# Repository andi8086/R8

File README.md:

## Picocom configuration ##

Start picocom with:

```
picocom --send-cmd "sx -Xb" -b 19200 -d 8 --emap lfcr /dev/ttyUSB0
```

## XMODEM File transfer ##

```
REICHEL R8
6502 CPU @ 2 MHz
32K RAM         
MONITOR (c)1976 Steve Wozniak
ADAPTED 2017 Andreas J. Reichel
\                              
F900R
F900: 20XMOD
CCCC
*** file: /home/andreas/Projects/6502/testprogs/test1.bin
$ sx -Xb /home/andreas/Projects/6502/testprogs/test1.bin 
Sending /home/andreas/Projects/6502/testprogs/test1.bin, 0 blocks: Give your local XMODEM receive command now.
Xmodem sectors/kbytes sent:   0/ 0kRetry 0: NAK on sector
Bytes Sent:    128   BPS:75                              

Transfer complete

*** exit status: 0 ***
OK
\
1000.1020
1000: A9 0E 85 20 A9 10 85 21
1008: 20 2F C0 4C 00 F8 48 69
1010: 2C 20 49 20 61 6D 20 74
1018: 68 65 20 66 69 72 73 74
1020: 20                     
1000    
1000: A9
Hi, I am the first program transfered via serial :)
\                                                  
```

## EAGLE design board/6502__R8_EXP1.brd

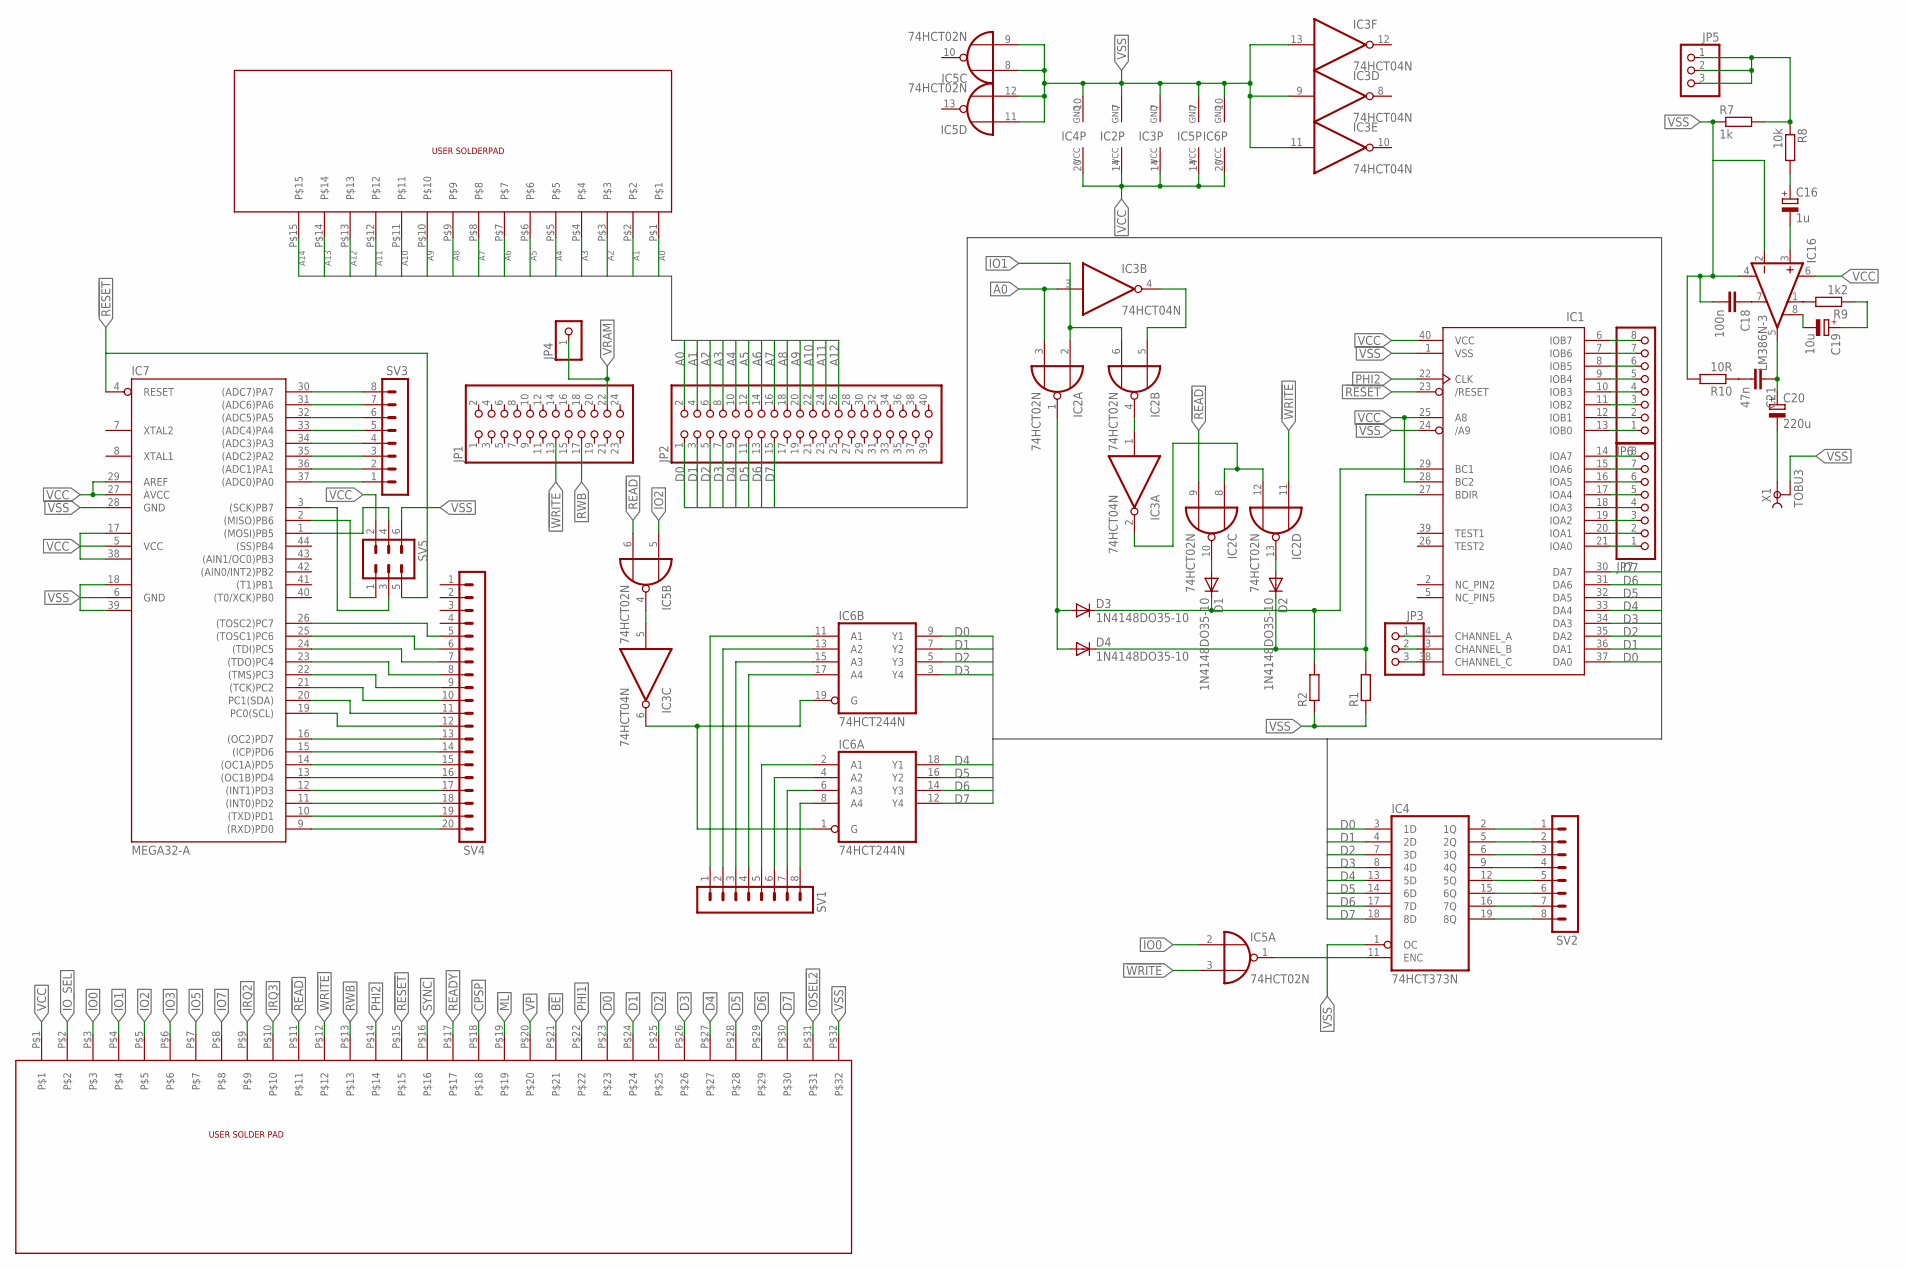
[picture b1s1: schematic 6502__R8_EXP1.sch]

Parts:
C16: 1u; E5-5
C18: 100n; C025-030X050
C19: 10u; E5-5
C20: 220u; E5-5
C21: 47n; C025-030X050
D1, D2, D3, D4: 1N4148DO35-10; DO35-10
IC1: AY-3-8910; DIL40
IC2, IC5: 74HCT02N; DIL14
IC3: 74HCT04N; DIL14
IC4: 74HCT373N; DIL20
IC6: 74HCT244N; DIL20
IC7: MEGA32-A; TQFP44
IC16: LM386N-3; DIL08
JP1: PINHD-2X12; 2X12
JP2: PINHD-2X20; 2X20
JP3, JP5: PINHD-1X3; 1X03
JP4: PINHD-1X1; 1X01
JP6, JP7: PINHD-1X8; 1X08
R1, R2: R-EU_0204/7; 0204/7
R7: 1k; 0207/12
R8: 10k; 0207/12
R9: 1k2; 0207/12
R10: 10R; 0207/12
SV1, SV2, SV3: MA08-1
SV4: MA20-1
SV5: MA03-2
U$2: SOLDERPAD
U$3: SOLDERPAD2
X1: TOBU3

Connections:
!BE: U$2.P$21
!IOSEL2: U$2.P$31
!ML: U$2.P$19
!READ: IC2.9 (I1), IC5.6 (I1), U$2.P$11
!RESET: IC1.23 (/RESET), IC7.4 (RESET), SV5.5, U$2.P$15
!VP: U$2.P$20
!VRAM: JP1.22, JP4.1
!WRITE: IC2.11 (I0), IC5.3 (I1), JP1.13, U$2.P$12
A0: IC2.3 (I1), IC3.3 (I), JP2.2, U$3.P$1
A1: JP2.4, U$3.P$2
A2: JP2.6, U$3.P$3
A3: JP2.8, U$3.P$4
A4: JP2.10, U$3.P$5
A5: JP2.12, U$3.P$6
A6: JP2.14, U$3.P$7
A7: JP2.16, U$3.P$8
A8: JP2.18, U$3.P$9
A9: JP2.20, U$3.P$10
A10: JP2.22, U$3.P$11
A11: JP2.24, U$3.P$12
A12: JP2.26, U$3.P$13
A13: U$3.P$14
A14: U$3.P$15
CPSP: U$2.P$18
D0: IC1.37 (DA0), IC4.3 (1D), IC6.9 (Y1), JP2.1, U$2.P$23
D1: IC1.36 (DA1), IC4.4 (2D), IC6.7 (Y2), JP2.3, U$2.P$24
D2: IC1.35 (DA2), IC4.7 (3D), IC6.5 (Y3), JP2.5, U$2.P$25
D3: IC1.34 (DA3), IC4.8 (4D), IC6.3 (Y4), JP2.7, U$2.P$26
D4: IC1.33 (DA4), IC4.13 (5D), IC6.18 (Y1), JP2.9, U$2.P$27
D5: IC1.32 (DA5), IC4.14 (6D), IC6.16 (Y2), JP2.11, U$2.P$28
D6: IC1.31 (DA6), IC4.17 (7D), IC6.14 (Y3), JP2.13, U$2.P$29
D7: IC1.30 (DA7), IC4.18 (8D), IC6.12 (Y4), JP2.15, U$2.P$30
IO0: IC5.2 (I0), U$2.P$3
IO1: IC2.2 (I0), IC2.6 (I1), U$2.P$4
IO2: IC5.5 (I0), U$2.P$5
IO3: U$2.P$6
IO5: U$2.P$7
IO7: U$2.P$8
IO_SEL: U$2.P$2
IRQ2: U$2.P$9
IRQ3: U$2.P$10
unnamed: IC4.11 (ENC), IC5.1 (O)
unnamed: IC6.11 (A1), SV1.1
unnamed: IC2.5 (I0), IC3.4 (O)
unnamed: IC2.4 (O), IC3.1 (I)
unnamed: IC2.8 (I0), IC2.12 (I1), IC3.2 (O)
unnamed: IC6.13 (A2), SV1.2
unnamed: D3.A, D4.A, IC2.1 (O)
unnamed: D1.C, D3.C, IC1.29 (BC1), R2.2
unnamed: D2.C, D4.C, IC1.27 (BDIR), R1.2
unnamed: D1.A, IC2.10 (O)
unnamed: D2.A, IC2.13 (O)
unnamed: IC6.15 (A3), SV1.3
unnamed: IC6.17 (A4), SV1.4
unnamed: IC6.2 (A1), SV1.5
unnamed: IC6.4 (A2), SV1.6
unnamed: IC6.6 (A3), SV1.7
unnamed: IC6.8 (A4), SV1.8
unnamed: IC3.5 (I), IC5.4 (O)
unnamed: IC3.6 (O), IC6.1 (G), IC6.19 (G)
unnamed: IC4.2 (1Q), SV2.1
unnamed: IC4.5 (2Q), SV2.2
unnamed: IC4.6 (3Q), SV2.3
unnamed: IC4.9 (4Q), SV2.4
unnamed: IC4.12 (5Q), SV2.5
unnamed: IC4.15 (6Q), SV2.6
unnamed: IC4.16 (7Q), SV2.7
unnamed: IC4.19 (8Q), SV2.8
unnamed: IC1.4 (CHANNEL_A), JP3.1
unnamed: IC1.3 (CHANNEL_B), JP3.2
unnamed: IC1.38 (CHANNEL_C), JP3.3
unnamed: IC1.13 (IOB0), JP6.1
unnamed: IC7.37 ((ADC0)PA0), SV3.1
unnamed: IC7.36 ((ADC1)PA1), SV3.2
unnamed: IC7.35 ((ADC2)PA2), SV3.3
unnamed: IC7.9 ((RXD)PD0), SV4.20
unnamed: IC7.10 ((TXD)PD1), SV4.19
unnamed: IC7.11 ((INT0)PD2), SV4.18
unnamed: IC7.12 ((INT1)PD3), SV4.17
unnamed: IC7.13 ((OC1B)PD4), SV4.16
unnamed: IC7.14 ((OC1A)PD5), SV4.15
unnamed: IC7.15 ((ICP)PD6), SV4.14
unnamed: IC7.16 ((OC2)PD7), SV4.13
unnamed: IC7.19 (PC0(SCL)), SV4.12
unnamed: IC7.20 (PC1(SDA)), SV4.11
unnamed: IC7.21 ((TCK)PC2), SV4.10
unnamed: IC7.22 ((TMS)PC3), SV4.9
unnamed: IC7.23 ((TDO)PC4), SV4.8
unnamed: IC7.24 ((TDI)PC5), SV4.7
unnamed: IC7.25 ((TOSC1)PC6), SV4.6
unnamed: IC7.26 ((TOSC2)PC7), SV4.5
unnamed: IC7.2 ((MISO)PB6), SV5.1
unnamed: IC7.3 ((SCK)PB7), SV5.3
unnamed: IC7.34 ((ADC3)PA3), SV3.4
unnamed: IC7.1 ((MOSI)PB5), SV5.4
unnamed: IC7.33 ((ADC4)PA4), SV3.5
unnamed: IC7.32 ((ADC5)PA5), SV3.6
unnamed: IC7.31 ((ADC6)PA6), SV3.7
unnamed: IC7.30 ((ADC7)PA7), SV3.8
unnamed: IC1.12 (IOB1), JP6.2
unnamed: IC1.11 (IOB2), JP6.3
unnamed: IC1.10 (IOB3), JP6.4
unnamed: IC1.9 (IOB4), JP6.5
unnamed: IC1.8 (IOB5), JP6.6
unnamed: IC1.7 (IOB6), JP6.7
unnamed: IC1.6 (IOB7), JP6.8
unnamed: IC1.21 (IOA0), JP7.1
unnamed: IC1.20 (IOA1), JP7.2
unnamed: IC1.19 (IOA2), JP7.3
unnamed: IC1.18 (IOA3), JP7.4
unnamed: IC1.17 (IOA4), JP7.5
unnamed: IC1.16 (IOA5), JP7.6
unnamed: IC1.15 (IOA6), JP7.7
unnamed: IC1.14 (IOA7), JP7.8
unnamed: JP5.1, JP5.2, JP5.3, R7.2, R8.1
unnamed: C16.+, R8.2
unnamed: C16.-, IC16.3 (+IN)
unnamed: C18.1, IC16.7 (BYPASS)
unnamed: C19.-, IC16.8 (GAIN)
unnamed: IC16.1 (GAIN), R9.2
unnamed: C19.+, R9.1
unnamed: C20.-, X1.1
unnamed: C20.+, C21.1, IC16.5 (OUT)
unnamed: C21.2, R10.1
PHI1: U$2.P$22
PHI2: IC1.22 (CLK), U$2.P$14
READY: U$2.P$17
RWB: JP1.17, U$2.P$13
SYNC: U$2.P$16
VCC: IC1.25 (A8), IC1.28 (BC2), IC1.40 (VCC), IC2.14 (VCC), IC3.14 (VCC), IC4.20 (VCC), IC5.14 (VCC), IC6.20 (VCC), IC7.5 (VCC), IC7.17 (VCC1), IC7.27 (AVCC), IC7.29 (AREF), IC7.38 (VCC2), IC16.6 (VS), SV5.2, U$2.P$1

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
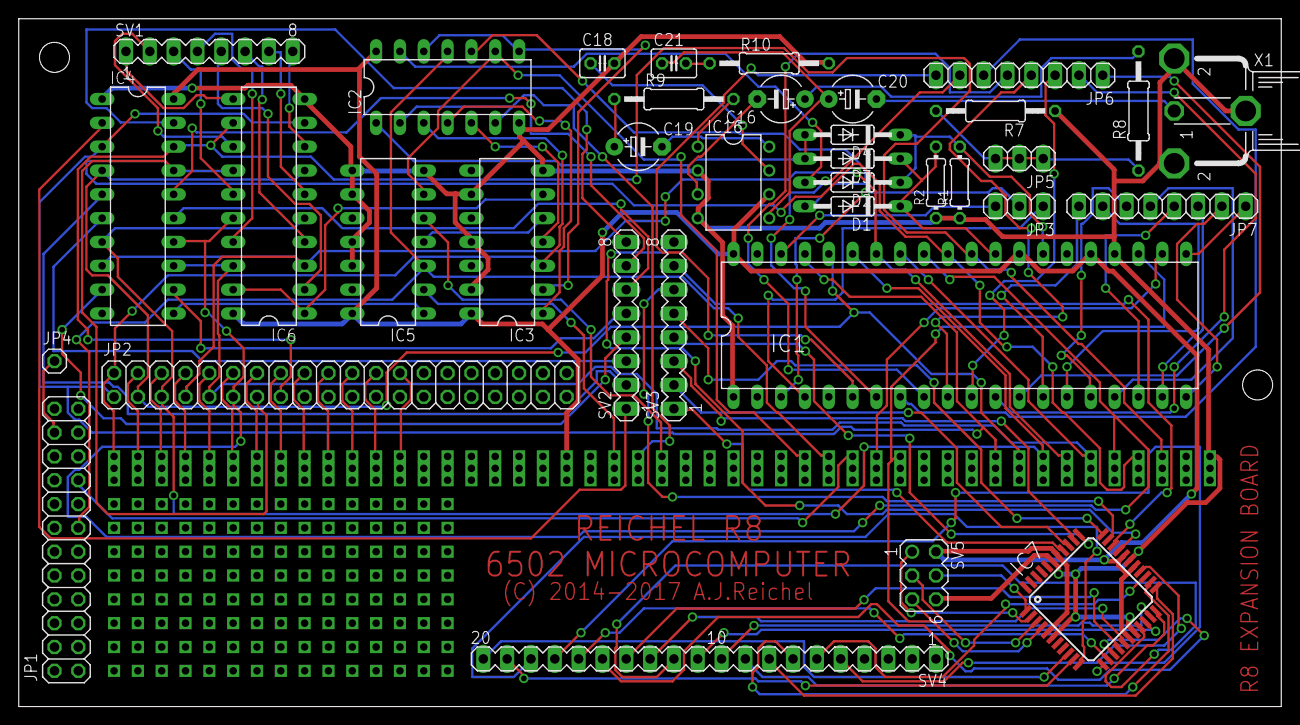
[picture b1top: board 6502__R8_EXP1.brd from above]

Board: 2 copper layers, 134.6 x 73.3 mm, 38 parts (0 on the bottom side), 115 nets.

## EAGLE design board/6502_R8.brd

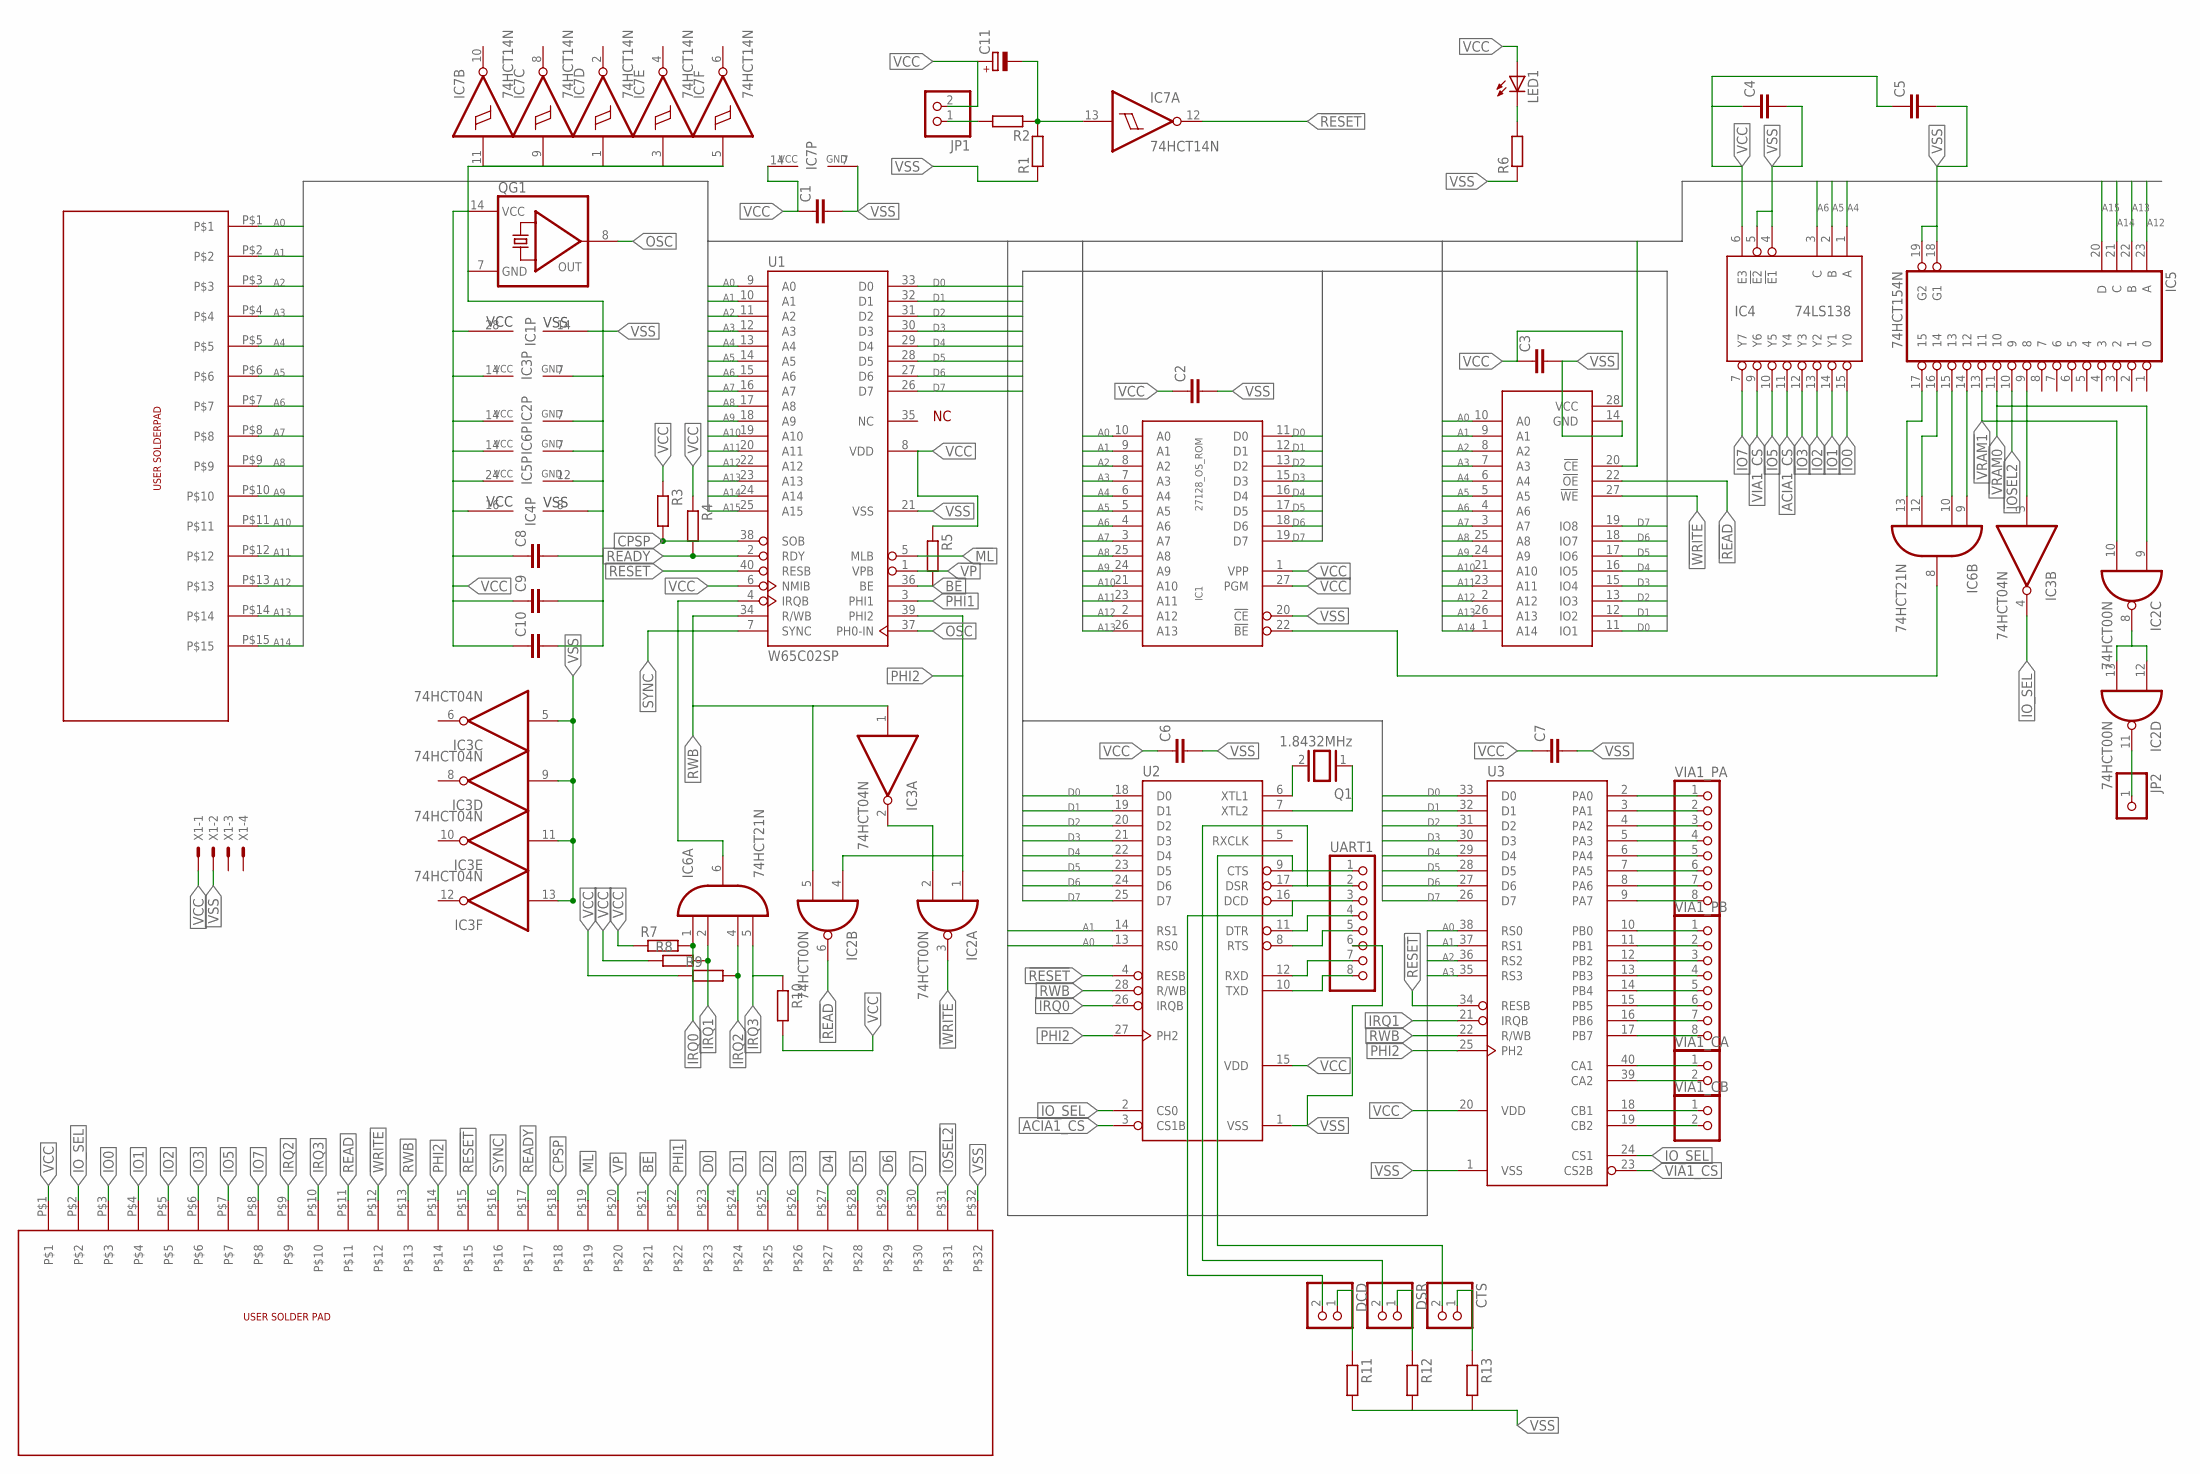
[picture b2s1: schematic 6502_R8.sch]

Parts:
C1, C2, C3, C4, C5, C6, C7, C8, C9, C10: C-EU025-024X044; C025-024X044
C11: CPOL-EUTT2D7; TT2D7
CTS: PINHD-1X2; 1X02
DCD: PINHD-1X2; 1X02
DSR: PINHD-1X2; 1X02
IC1: 27128_OS_ROM; DIL28
IC2: 74HCT00N; DIL14
IC3: 74HCT04N; DIL14
IC4: 74LS138; DIL16
IC5: 74HCT154N; DIL24-6
IC6: 74HCT21N; DIL14
IC7: 74HCT14N; DIL14
JP1: PINHD-1X2; 1X02
JP2: PINHD-1X1; 1X01
LED1: LED5MM
Q1: 1.8432MHz; Q
QG1: QG5860; DIL14S
R1, R2, R3, R4, R5, R6, R7, R8, R9, R10, R11, R12, R13: R-EU_0207/7; 0207/7
U1: W65C02SP; DIP-40
U2: G65SC51P; DIP-28
U3: G65SC22P; DIP-40
U$1: CXK58258AP-20; DIL28-3
U$2: SOLDERPAD
U$3: SOLDERPAD2
UART1: PINHD-1X8; 1X08
VIA1_CA, VIA1_CB: PINHD-1X2; 1X02
VIA1_PA, VIA1_PB: PINHD-1X8; 1X08
X1: KK-156-4

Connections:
!BE: U$2.P$21
!IOSEL2: IC5.10 (9), U$2.P$31
!ML: U1.5 (MLB), U$2.P$19
!READ: IC2.6 (O), U$1.22 (!OE), U$2.P$11
!RESET: IC7.12 (O), U1.40 (RESB), U2.4 (RESB), U3.34 (RESB), U$2.P$15
!VP: U1.1 (VPB), U$2.P$20
!VRAM0: IC2.9 (I0), IC5.11 (10)
!VRAM1: IC2.10 (I1), IC5.13 (11)
!WRITE: IC2.3 (O), U$1.27 (!WE), U$2.P$12
A0: IC1.10 (A0), U1.9 (A0), U2.13 (RS0), U3.38 (RS0), U$1.10 (A0), U$3.P$1
A1: IC1.9 (A1), U1.10 (A1), U2.14 (RS1), U3.37 (RS1), U$1.9 (A1), U$3.P$2
A2: IC1.8 (A2), U1.11 (A2), U3.36 (RS2), U$1.8 (A2), U$3.P$3
A3: IC1.7 (A3), U1.12 (A3), U3.35 (RS3), U$1.7 (A3), U$3.P$4
A4: IC1.6 (A4), IC4.1 (A), U1.13 (A4), U$1.6 (A4), U$3.P$5
A5: IC1.5 (A5), IC4.2 (B), U1.14 (A5), U$1.5 (A5), U$3.P$6
A6: IC1.4 (A6), IC4.3 (C), U1.15 (A6), U$1.4 (A6), U$3.P$7
A7: IC1.3 (A7), U1.16 (A7), U$1.3 (A7), U$3.P$8
A8: IC1.25 (A8), U1.17 (A8), U$1.25 (A8), U$3.P$9
A9: IC1.24 (A9), U1.18 (A9), U$1.24 (A9), U$3.P$10
A10: IC1.21 (A10), U1.19 (A10), U$1.21 (A10), U$3.P$11
A11: IC1.23 (A11), U1.20 (A11), U$1.23 (A11), U$3.P$12
A12: IC1.2 (A12), IC5.23 (A), U1.22 (A12), U$1.2 (A12), U$3.P$13
A13: IC1.26 (A13), IC5.22 (B), U1.23 (A13), U$1.26 (A13), U$3.P$14
A14: IC5.21 (C), U1.24 (A14), U$1.1 (A14), U$3.P$15
A15: IC5.20 (D), U1.25 (A15), U$1.20 (!CE)
ACIA1_CS: IC4.11 (Y4), U2.3 (CS1B)
BE: R5.2, U1.36 (BE)
CPSP: R3.2, U1.38 (SOB), U$2.P$18
D0: IC1.11 (D0), U1.33 (D0), U2.18 (D0), U3.33 (D0), U$1.11 (IO1), U$2.P$23
D1: IC1.12 (D1), U1.32 (D1), U2.19 (D1), U3.32 (D1), U$1.12 (IO2), U$2.P$24
D2: IC1.13 (D2), U1.31 (D2), U2.20 (D2), U3.31 (D2), U$1.13 (IO3), U$2.P$25
D3: IC1.15 (D3), U1.30 (D3), U2.21 (D3), U3.30 (D3), U$1.15 (IO4), U$2.P$26
D4: IC1.16 (D4), U1.29 (D4), U2.22 (D4), U3.29 (D4), U$1.16 (IO5), U$2.P$27
D5: IC1.17 (D5), U1.28 (D5), U2.23 (D5), U3.28 (D5), U$1.17 (IO6), U$2.P$28
D6: IC1.18 (D6), U1.27 (D6), U2.24 (D6), U3.27 (D6), U$1.18 (IO7), U$2.P$29
D7: IC1.19 (D7), U1.26 (D7), U2.25 (D7), U3.26 (D7), U$1.19 (IO8), U$2.P$30
IO0: IC4.15 (Y0), U$2.P$3
IO1: IC4.14 (Y1), U$2.P$4
IO2: IC4.13 (Y2), U$2.P$5
IO3: IC4.12 (Y3), U$2.P$6
IO5: IC4.10 (Y5), U$2.P$7
IO7: IC4.7 (Y7), U$2.P$8
IO_SEL: IC3.4 (O), U2.2 (CS0), U3.24 (CS1), U$2.P$2
IRQ0: IC6.1 (I0), R7.2, U2.26 (IRQB)
IRQ1: IC6.2 (I1), R8.2, U3.21 (IRQB)
IRQ2: IC6.4 (I2), R9.2, U$2.P$9
IRQ3: IC6.5 (I3), R10.1, U$2.P$10
unnamed: IC3.3 (I), IC5.9 (8)
unnamed: IC5.17 (15), IC6.13 (I3)
unnamed: IC5.16 (14), IC6.12 (I2)
unnamed: IC5.15 (13), IC6.10 (I1)
unnamed: IC5.14 (12), IC6.9 (I0)
unnamed: IC1.22 (!BE), IC6.8 (O)
unnamed: IC2.2 (I1), IC3.2 (O)
unnamed: Q1.2, U2.6 (XTL1)
unnamed: Q1.1, U2.7 (XTL2)
unnamed: IC6.6 (O), U1.4 (IRQB)
unnamed: IC2.8 (O), IC2.12 (I0), IC2.13 (I1)
unnamed: IC2.11 (O), JP2.1
unnamed: U3.2 (PA0), VIA1_PA.1
unnamed: C11.-, IC7.13 (I), R1.2, R2.1
unnamed: JP1.1, R2.2
unnamed: U3.3 (PA1), VIA1_PA.2
unnamed: U3.4 (PA2), VIA1_PA.3
unnamed: LED1.K (C), R6.2
unnamed: U3.5 (PA3), VIA1_PA.4
unnamed: U3.6 (PA4), VIA1_PA.5
unnamed: U3.7 (PA5), VIA1_PA.6
unnamed: U3.8 (PA6), VIA1_PA.7
unnamed: U3.9 (PA7), VIA1_PA.8
unnamed: U3.10 (PB0), VIA1_PB.1
unnamed: U3.11 (PB1), VIA1_PB.2
unnamed: U3.12 (PB2), VIA1_PB.3
unnamed: U3.13 (PB3), VIA1_PB.4
unnamed: U3.14 (PB4), VIA1_PB.5
unnamed: U3.15 (PB5), VIA1_PB.6
unnamed: U3.16 (PB6), VIA1_PB.7
unnamed: U3.17 (PB7), VIA1_PB.8
unnamed: U3.40 (CA1), VIA1_CA.1
unnamed: U3.39 (CA2), VIA1_CA.2
unnamed: U3.18 (CB1), VIA1_CB.1
unnamed: U3.19 (CB2), VIA1_CB.2
unnamed: U2.10 (TXD), UART1.8
unnamed: U2.12 (RXD), UART1.7
unnamed: CTS.2, U2.9 (CTS), UART1.1
unnamed: DSR.2, U2.17 (DSR), UART1.2
unnamed: DCD.2, U2.16 (DCD), UART1.3
unnamed: U2.11 (DTR), UART1.4
unnamed: U2.8 (RTS), UART1.5
unnamed: DCD.1, R11.1
unnamed: DSR.1, R12.1
unnamed: CTS.1, R13.1
OSC: QG1.8 (OUT), U1.37 (PH0-IN)
PHI1: U1.3 (PHI1), U$2.P$22
PHI2: IC2.1 (I0), IC2.4 (I0), U1.39 (PHI2), U2.27 (PH2), U3.25 (PH2), U$2.P$14
READY: R4.2, U1.2 (RDY), U$2.P$17
RWB: IC2.5 (I1), IC3.1 (I), U1.34 (R/WB), U2.28 (R/WB), U3.22 (R/WB), U$2.P$13
SYNC: U1.7 (SYNC), U$2.P$16
VCC: C1.1, C2.1, C3.1, C4.1, C5.1, C6.1, C7.1, C8.1, C9.1, C10.1, C11.+, IC1.1 (VPP), IC1.27 (PGM), IC1.28 (VCC), IC2.14 (VCC), IC3.14 (VCC), IC4.6 (E3), IC4.16 (VCC), IC5.24 (VCC), IC6.14 (VCC), IC7.14 (VCC), JP1.2, LED1.A, QG1.14 (VCC), R3.1, R4.1, R5.1, R7.1, R8.1, R9.1, R10.2, U1.6 (NMIB), U1.8 (VDD), U2.15 (VDD), U3.20 (VDD), U$1.28 (VCC), U$2.P$1, X1.1
VIA1_CS: IC4.9 (Y6), U3.23 (CS2B)
VSS: C1.2, C2.2, C3.2, C4.2, C5.2, C6.2, C7.2, C8.2, C9.2, C10.2, IC1.14 (VSS), IC1.20 (!CE), IC2.7 (GND), IC3.5 (I), IC3.7 (GND), IC3.9 (I), IC3.11 (I), IC3.13 (I), IC4.4 (!E1), IC4.5 (!E2), IC4.8 (VSS), IC5.12 (GND), IC5.18 (G1), IC5.19 (G2), IC6.7 (GND), IC7.1 (I), IC7.3 (I), IC7.5 (I), IC7.7 (GND), IC7.9 (I), IC7.11 (I), QG1.7 (GND), R1.1, R6.1, R11.2, R12.2, R13.2, U1.21 (VSS), U2.1 (VSS), U3.1 (VSS), U$1.14 (GND), U$2.P$32, UART1.6, X1.2

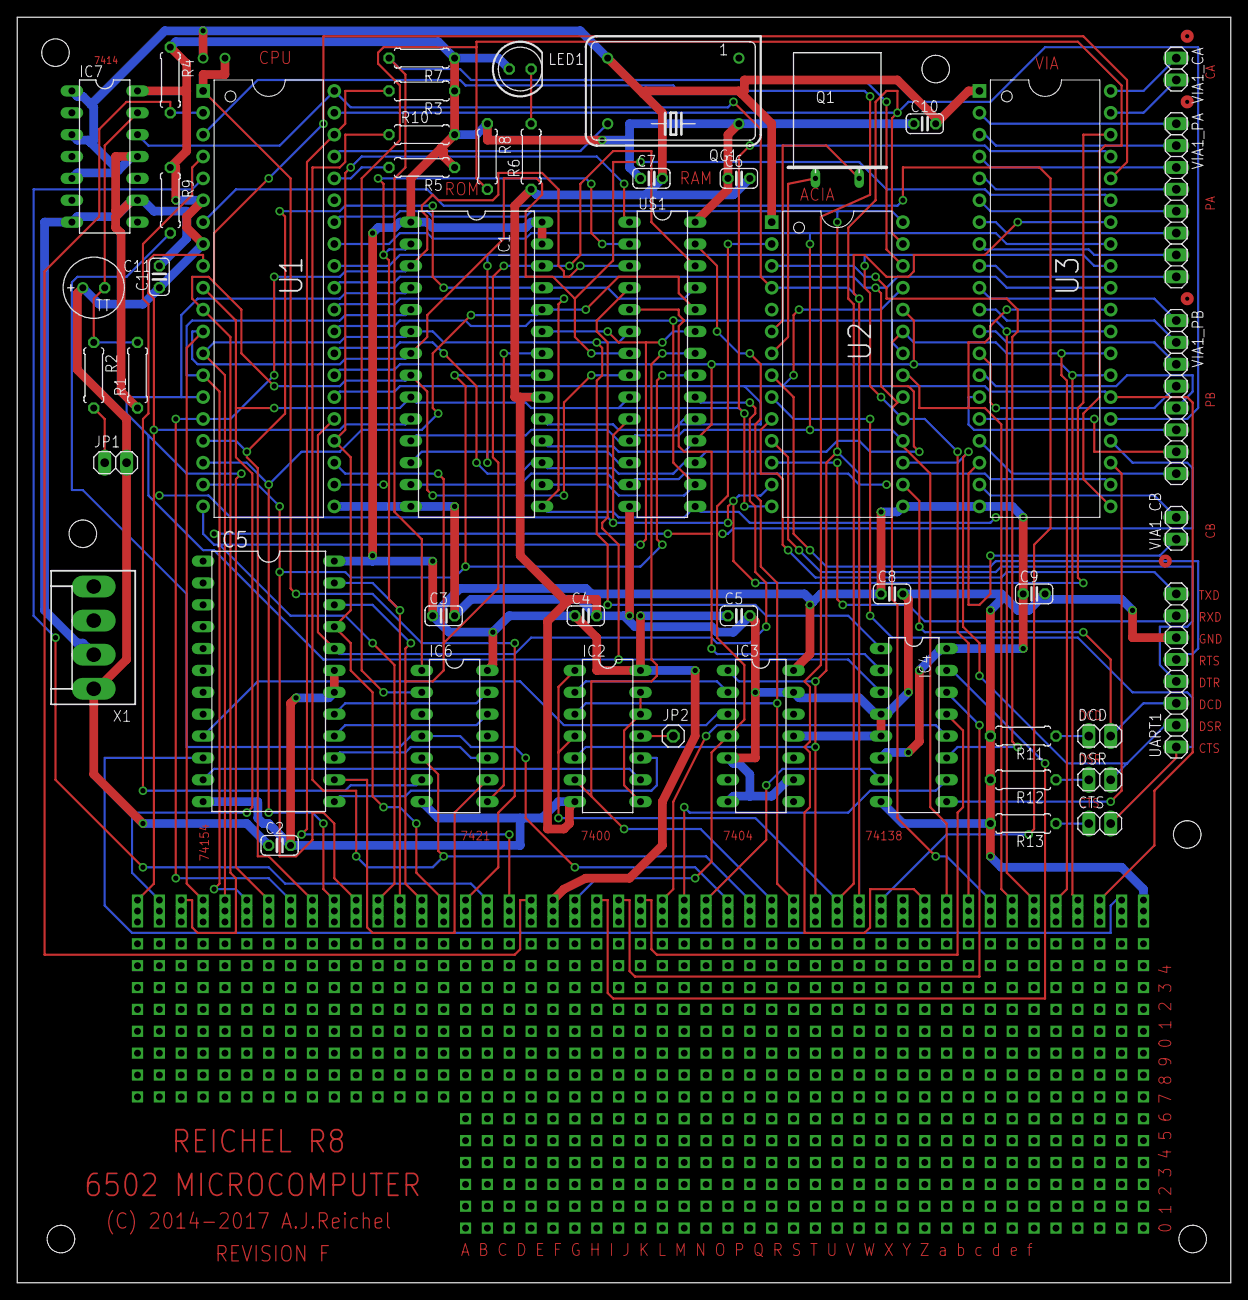
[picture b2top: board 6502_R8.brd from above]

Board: 2 copper layers, 140.9 x 147.0 mm, 51 parts (0 on the bottom side), 100 nets.

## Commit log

2017-04-28 Initial commit
    Initial commit
2017-04-28 Numeric variable set: Repair wrong FP config
    CBM-BASIC Version 2 does apparently not work with
    smaller FP definition. So just use the bigger one
    with more precision :)
2017-04-28 LOAD: Add load command
    Add a print clone as load command to start string parsing
2017-04-28 LOAD: simplify string extraction
    Parse only one string, everything else is an error.
    String-evaluating expressions are allowed :)
2017-04-28 ZP: move basic variables to above $40
    allow permanent kernal space below $40 which should
    not get scrambled by BASIC
2017-04-28 Makefile: Output entry of BASIC
    Parse BASIC entry point out of map file.
2017-04-28 PRINT: Fix newline bug with ","
    PRINT added a superfluous new line character after every "," and
    after the end of the output.
2017-04-28 ERROR: Fix corrupted second ERR letter
    Second error code letter got corrupted by not being
    anded with $7F
2017-04-28 LOAD: Add Index function and FN Pointer
    Use Kernal ZP variable to store FN Pointer
    Use "$" to access directory of disk
2017-04-28 FILE I/O: Add Kernal Stubs for Channel management
    PRINT# and INPUT# need CHKIN, CHKOUT, CLRCH
2017-05-03 keyboard: Add firmware to scan C64 keyboard
    Add firmware for keyboard controller
2017-07-06 basic: Simplify input ifdefs
2017-07-06 xmodem: Remove CRC checking and EOT check
2017-07-06 Add README.md
2017-07-09 xmodem: reenable target address from image
2017-07-09 msbasic: Correct long FP values for trig functions
2017-07-09 msbasic: Correct memory address of entropy to IO space
2017-07-09 Add RAM version of basic for development
2017-07-09 FIX BUG: Fix reset bug on basic start
    CLALL was not defined in KERNAL!
2017-07-09 major update: xmodem basic
    xmodem: remove crc stuff to save space
    basic: add clall kernal routine to prevent boot crash
2017-07-10 Expansion board: Add layout and schematics
    * Keyboard Connector
    * Sound Generator
    * Graphics Interface
    * Control Registers
2017-07-12 Expansion board: Improve Layout, Fix Errors
2017-12-30 basic: Add missing file
    Add missing r8file.s
2017-12-30 Add character generator
    use 6x8 font and rotate characters to only use 192 bytes
    for all 256 codes.
2017-12-31 Add listing file generation for basic
    Generate a listing when compiling
    msbasic.
2017-12-31 Initialize System control port on startup
    Call init_SYSCTRL from main before ACIA
    init.
2017-12-31 Add some video code to ROM
    Add clrscr and syncwait to ROM
2017-12-31 Add listing generation to all .o files
    Generate listings for all .s files
2017-12-31 Add zp.inc for zero page definitions
2017-12-31 Add system.inc for port definitions
2018-01-02 Add Character Generation Function
    Add needed multiplication function
    Add offset calculation function
    Add character render function
2018-01-03 Add RGA Firmware to source tree
    Add the files for the RGA Firmware on the
    ATmega168.
2018-01-03 Rewrite RGA firmware to display whole picture
    Remove empty scanline after each scanline.
2018-01-03 Fix bank switching in characater rendering
    Bank switching must occur if High-Byte is
    greater or equal to #$C0. It does not occur
    if it is smaller or equal to #$BF.
2018-01-03 Add basic RGA character functions
2018-01-05 Add color to char render test func
    Render characters in all available colors
    foreground and background.
2018-01-05 rga: tidy up firmware code
    Tidy up code and remove code relicts
2018-01-05 RGA: create separate simulation script
    Remove simulator start line from make.sh
2018-01-05 RGA: Correct pinout description in main.s header
    Mention new pinout in header first
2018-01-05 RGA: Bugfix: Don't allow CPU access between display lines
    CPU can be sure to have 9.84 ms time to write to VRAM in
    each VLOCK-low period.
2018-01-06 rga: accelerate functions and implement scrollup
    Accelerate clrscr to only sync when out of time
    Accelerate render chars test function
    Implement scroll up function.
2018-01-06 Fix scrollup function
    Source starts at A690, i.e. it is not divisible by 256, which
    causes a bank switch inside the copy loop which is not possible
    due to timing restrictions. Thus, we have to stop one page
    before the bank end and do the rest in two extra loops.
2018-01-06 RGA: Paint last line with background color
    After scrolling up, last line is filled with
    active background color
2018-01-06 Enhance rga_putc and activate character output
    Now also output characters to screen as well
2018-01-06 Sync for each character sent to rga
    Add forgotten sync call to rga_putc
2018-01-07 Use X Register for Bank switching in scroll func
    Use X Register to faster switch between banks to
    speed up scroll function and reduce code size.
2018-01-07 Fix errors in scrollup and remove unneeded newline before boot msg
    Fix errors in scrollup function and remove unneeded CR LF before
    the boot message.
2018-01-07 RGA: Fix firmware counter control
    In the first line, we start clocking the address counter, which
    means, the first pixel comes from address 1, and not 0. Thus, in the
    very first scan line, we have to do only 209 pixels instead of 210,
    so that the picture gets mapped to the SRAM correctly.
2018-10-23 Always build rom.bin, make it a phony target

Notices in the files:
board/6502_R8.brd:
(C) 2014-2017 A.J.Reichel
parts and their libraries:
eagle-6.5.0-atari: Copyright (c) 2010
Copyright (c) 2009
This library is licensed under the
Creative Commons Attribution 3.0 United States License.
